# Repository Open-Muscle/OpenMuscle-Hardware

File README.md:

# 🛠️ OpenMuscle-Hardware (Deprecated)

> ⚠️ **This repository is no longer maintained.**  
> All hardware design files have been **moved to dedicated repositories** for each OpenMuscle device.  
> Please use the links below to access the latest versions, schematics, and BOMs.

---

## 📦 Where to Find Active Repositories

| Device | Description | New Repo |
|--------|-------------|----------|
| **FlexGrid** | 60-sensor modular wearable (successor to OM-12) | [OpenMuscle-FlexGrid](https://github.com/Open-Muscle/OpenMuscle-FlexGrid) |
| **LASK5** | Handheld labeler wand for gesture training | [OpenMuscle-LASK5](https://github.com/Open-Muscle/OpenMuscle-LASK5) |
| **OM-12** | Legacy 12-sensor forearm band | [OpenMuscle-Band](https://github.com/Open-Muscle/OpenMuscle-Band) |
| **Firmware & Scripts** | MicroPython code for all devices | [OpenMuscle-Software](https://github.com/Open-Muscle/OpenMuscle-Software) |
| **Documentation** | Central hub with build guides & tutorials | [OpenMuscle-Hub](https://github.com/Open-Muscle/OpenMuscle-Hub) |

---

## 🧬 About This Repo

This repository originally contained hardware design files for two experimental devices:

- **OpenMuscle Labeler** – A handheld interface for labeling finger positions in machine learning datasets.
- **OpenMuscle Sensor Bracelet (OM-12)** – A pressure-based forearm sensor for capturing muscle signals.

These designs are preserved in their new locations above for better modularity and long-term maintainability.

---

## 🧾 Historical Reference

This repo includes:
- `Labeler/`: KiCad files and documents for early LASK prototypes
- `SensorBracelet/`: KiCad files and mechanical designs for OM-12
- `docs/`: Revision notes and changelogs

---

## 📜 License

This repository is licensed under the **CERN-OHL-S v2** (Strongly Reciprocal).

"""markdown
🔗 Learn more at the [Open Source Hardware Association (OSHWA)](https://www.oshwa.org/definition/)
"""

OpenMuscle is an OSHWA-Certified open hardware project  
**Certification UID:** US002537

---

## 🙌 Thank You

Thank you to everyone who starred, forked, contributed to, or studied this repository during its development phase.  
Please visit the [OpenMuscle GitHub Organization](https://github.com/Open-Muscle) to explore the new, modular layout and latest devices.

🧠 Built by [@TURFPTAx](https://github.com/turfptax) • Project home: [openmuscle.org](https://openmuscle.org)

## 🎥 Video Overview

Curious about the assembly process? Watch our detailed video guide covering both the Sensor Bracelet (OM-12) and Labeler (LASK5) builds:  
📺 **[Watch on YouTube](https://www.youtube.com/watch?v=DQQq6cplsOw)**

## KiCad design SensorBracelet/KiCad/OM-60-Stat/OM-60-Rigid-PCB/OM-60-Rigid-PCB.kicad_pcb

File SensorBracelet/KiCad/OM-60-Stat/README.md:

# OpenMuscle FlexGrid (v2.0)

**OpenMuscle FlexGrid** is a modular wearable sensor grid with 60 analog pressure sensors arranged in a 15x4 matrix. It is the second-generation wearable in the OpenMuscle series and serves as the core interface for capturing muscle movement in prosthetic and robotics applications.

📍 Project Page: [openmuscle.org](https://openmuscle.org)

---

## 📐 System Overview

- **Sensor Grid**: 15 columns × 4 rows of Velostat pads
- **Flex PCB**: Thin and wearable with 21-pin output header
- **Rigid PCB**: ESP32-S3, haptic feedback, USB-C charging, multiplexer, OLED, IMU

---

## 🔧 Key Features

| Feature               | Description                                  |
|-----------------------|----------------------------------------------|
| MCU                   | ESP32-S3 (USB + BLE + ADC1)                  |
| Sensor Matrix         | 15×4 Velostat with voltage divider setup     |
| Multiplexer           | 74HC4067 (16-channel, 15 used)               |
| Row Reads             | 4x analog inputs on ADC1                     |
| OLED Display          | SSD1306 128x32 over I2C                      |
| IMU                   | ICM-42688-P 6-DOF sensor (optional)          |
| Haptic Feedback       | Motor driven by IRLML2060 MOSFET             |
| Power Management      | MAX16054 soft latch, TPS7A0333 LDO, LTC4054 LiPo charger |

---

## 🗂️ File Structure

```graphql
FlexGrid/
├── KiCad/ # Schematic and layout files
├── Images/ # Renders and photos
├── BOM.xlsx # Bill of materials (optional)
└── README.md # You're reading it!
```

# 📁 Repository Layout

```graphql
OpenMuscle-FlexGrid/
├── firmware/           # MicroPython or C code for scanning and I/O
├── hardware/
│   ├── KiCad/          # Schematics, PCB, BOMs
│   └── Images/         # Renders and assembly diagrams
├── docs/
│   └── Datasheets/     # ICs and reference materials
└── README.md
```
---

## 🛠️ How It Works

The 74HC4067 connects one column at a time to 3.3V. The Velostat pads act as pressure-sensitive resistors connected to row lines, which are pulled down with 10kΩ resistors and read via analog inputs.

A software loop cycles through all 15 columns, sampling all 4 rows each time for 60 total readings per frame.

---

## 🧪 Status

- ✅ Schematic Complete
- ✅ PCB Fabricated & Assembled
- 🛠️ Firmware In Progress
- 🧠 ML Integration Pipeline Active

---

## 🔗 Related Projects

- [SensorBracelet (OM-12)](../SensorBracelet/)
- [Labeler (LASK5)](../Labeler/)

---

## 📝 License

- **Hardware**: CERN-OHL-P v2
- **Software/Firmware**: MIT

---

## 🤝 Get Involved

We welcome contributions, feedback, and forks. This project is part of a broader mission to open-source biomechanical sensing tools for all.

Visit **[openmuscle.org](https://openmuscle.org)** or join our Discord (link coming soon).

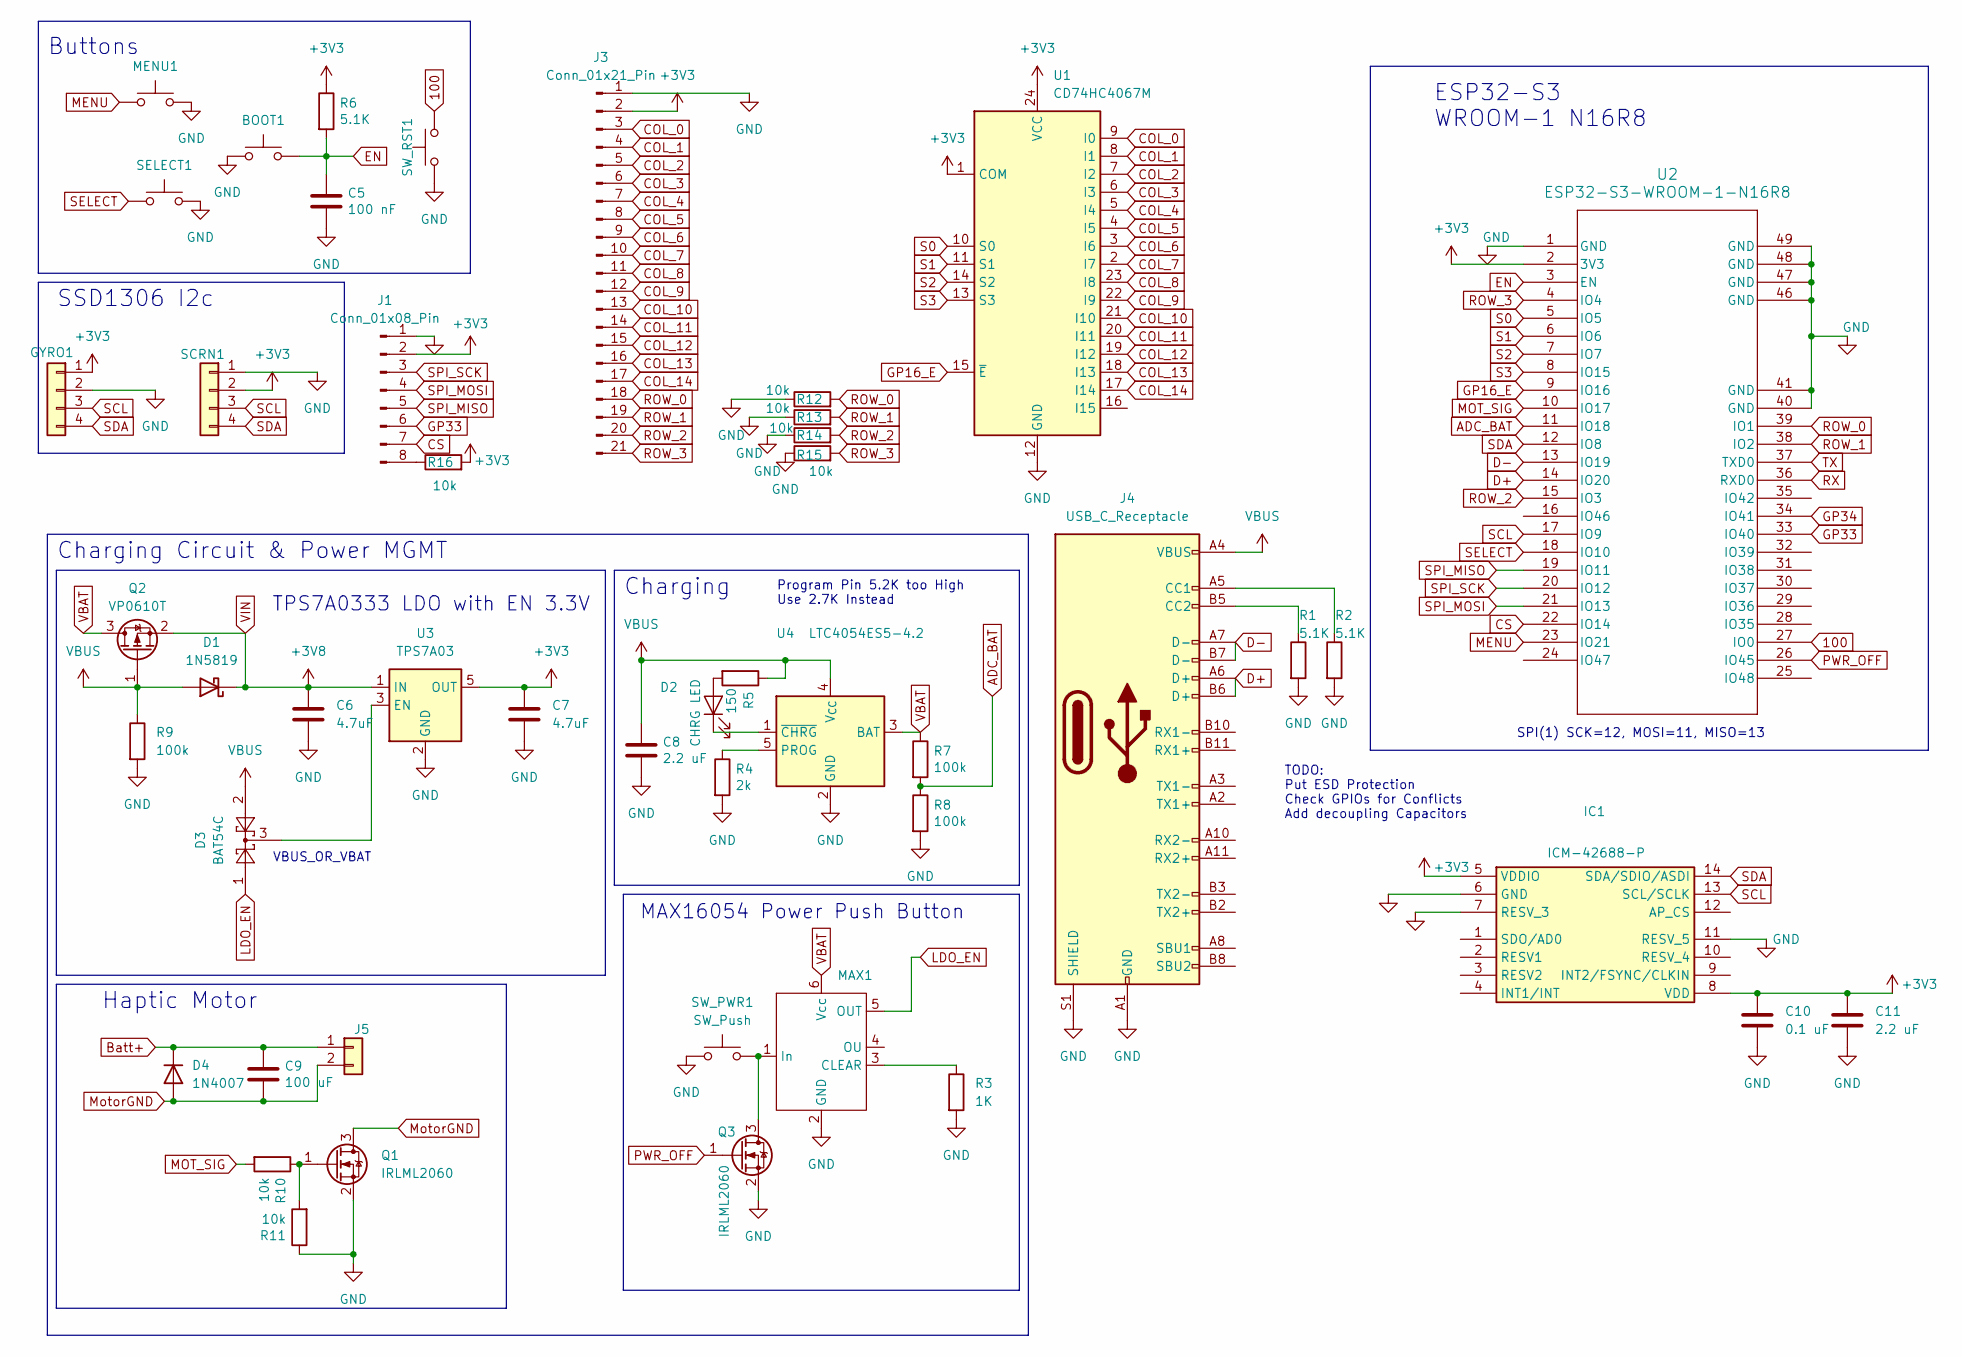
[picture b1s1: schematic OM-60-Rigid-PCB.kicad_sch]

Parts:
BOOT1: SW_Push; EVQP2P02M
C5: 100 nF; C_0402_1005Metric; JLCPN C1525
C6, C7: 4.7uF; C_0805_2012Metric
C8: 2.2 uF; C_0603_1608Metric; JLCPN C12530
C9: 100 uF; C_0603_1608Metric; JLCPN C12530
C10: 0.1 uF; C_0603_1608Metric
C11: 2.2 uF; C_0603_1608Metric
D1: 1N5819; D_SOD-123F
D2: CHRG LED; LED_0805_2012Metric; JLCPN C72043
D3: BAT54C; SOT-23
D4: 1N4007; D_SOD-123
GYRO1: Conn_01x04; PinHeader_1x04_P2.54mm_Vertical
IC1: ICM-42688-P; IIM42352; Mouser Part Number 410-ICM-42688-P
J1: Conn_01x08_Pin; PinHeader_1x08_P2.54mm_Vertical
J3: Conn_01x21_Pin; PinSocket_1x21_P2.54mm_Vertical
J4: USB_C_Receptacle; USB_C_Receptacle_HRO_TYPE-C-31-M-12
J5: Conn_01x02; PinHeader_1x02_P2.00mm_Vertical
MAX1: SOT-23-6
MENU1: SW_Push; EVQP2P02M
Q1, Q3: IRLML2060; SOT-23
Q2: VP0610T; SOT-23
R1, R2, R6: 5.1K; R_0603_1608Metric; JLCPN C25905
R3: 1K; R_0603_1608Metric
R4: 2k; R_0603_1608Metric; JLCPN C25905
R5: 150; R_0603_1608Metric; JLCPN C4109
R7, R8: 100k; R_0603_1608Metric; JLCPN C25905
R9: 100k; R_0603_1608Metric
R10, R11: 10k; R_0603_1608Metric; JLCPN C25744
R12, R13, R14, R15, R16: 10k; R_0603_1608Metric; JLCPN C25905
SCRN1: Conn_01x04; PinHeader_1x04_P2.54mm_Vertical
SELECT1: SW_Push; EVQP2P02M
SW_PWR1: SW_Push; EVQP2P02M
SW_RST1: SW_Push; EVQP2P02M
U1: CD74HC4067M; SOIC-24W_7.5x15.4mm_P1.27mm
U2: ESP32-S3-WROOM-1-N16R8
U3: TPS7A03; SOT-23-5
U4: LTC4054ES5-4.2; TSOT-23-5

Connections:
100: SW_RST1.2, U2.27 (IO0)
+3V3: C7.1, C10.1, C11.1, GYRO1.1, IC1.5 (VDDIO), IC1.8 (VDD), J1.2, J3.2, R6.1, R16.2, SCRN1.2, U1.1 (COM), U1.24 (VCC), U2.2 (3V3), U3.5 (OUT)
ADC_BAT: R7.2, R8.1, U2.11 (IO18)
Batt+: C9.2, D4.1 (K), J5.1
COL_0: J3.3, U1.9 (I0)
COL_1: J3.4, U1.8 (I1)
COL_2: J3.5, U1.7 (I2)
COL_3: J3.6, U1.6 (I3)
COL_4: J3.7, U1.5 (I4)
COL_5: J3.8, U1.4 (I5)
COL_6: J3.9, U1.3 (I6)
COL_7: J3.10, U1.2 (I7)
COL_8: J3.11, U1.23 (I8)
COL_9: J3.12, U1.22 (I9)
COL_10: J3.13, U1.21 (I10)
COL_11: J3.14, U1.20 (I11)
COL_12: J3.15, U1.19 (I12)
COL_13: J3.16, U1.18 (I13)
COL_14: J3.17, U1.17 (I14)
CS: J1.7, U2.22 (IO14)
D+: J4.A6 (D+), J4.B6 (D+), U2.14 (IO20)
D-: J4.A7 (D-), J4.B7 (D-), U2.13 (IO19)
EN: BOOT1.2, C5.2, R6.2, U2.3 (EN)
GND: BOOT1.1, C5.1, C6.2, C7.2, C8.1, C10.2, C11.2, GYRO1.2, IC1.6 (GND), IC1.7 (RESV_3), IC1.11 (RESV_5), J1.1, J3.1, J4.A1 (GND), J4.A12 (GND), J4.B1 (GND), J4.B12 (GND), J4.S1 (SHIELD), MAX1.2 (GND), MENU1.2, Q1.2 (S), Q3.2 (S), R1.2, R2.2, R3.2, R4.2, R8.2, R9.2, R11.1, R12.1, R13.1, R14.1, R15.1, SCRN1.1, SELECT1.2, SW_PWR1.1, SW_RST1.1, U1.12 (GND), U2.1 (GND), U2.40 (GND), U2.41 (GND), U2.46 (GND), U2.47 (GND), U2.48 (GND), U2.49 (GND), U3.2 (GND), U4.2 (GND)
GP16_E: U1.15 (~E), U2.9 (IO16)
GP33: J1.6, U2.33 (IO40)
GP34: U2.34 (IO41)
LDO_EN: D3.1, MAX1.5 (OUT)
MENU: MENU1.1, U2.23 (IO21)
MOT_SIG: R10.2, U2.10 (IO17)
MotorGND: C9.1, D4.2 (A), J5.2, Q1.3 (D)
unnamed: D2.2 (A), R5.2
unnamed: D2.1 (K), U4.1 (~CHRG)
unnamed: J1.8, R16.1
unnamed: J4.A5 (CC1), R2.1
unnamed: J4.B5 (CC2), R1.1
unnamed: MAX1.3 (CLEAR), R3.1
unnamed: MAX1.1 (In), Q3.3 (D), SW_PWR1.2
unnamed: Q1.1 (G), R10.1, R11.2
unnamed: D3.3, U3.3 (EN)
unnamed: R4.1, U4.5 (PROG)
PWR_OFF: Q3.1 (G), U2.26 (IO45)
ROW_0: J3.18, R12.2, U2.39 (IO1)
ROW_1: J3.19, R13.2, U2.38 (IO2)
ROW_2: J3.20, R14.2, U2.15 (IO3)
ROW_3: J3.21, R15.2, U2.4 (IO4)
RX: U2.36 (RXD0)
S0: U1.10 (S0), U2.5 (IO5)
S1: U1.11 (S1), U2.6 (IO6)
S2: U1.14 (S2), U2.7 (IO7)
S3: U1.13 (S3), U2.8 (IO15)
SCL: GYRO1.3, IC1.13 (SCL/SCLK), SCRN1.3, U2.17 (IO9)
SDA: GYRO1.4, IC1.14 (SDA/SDIO/ASDI), SCRN1.4, U2.12 (IO8)
SELECT: SELECT1.1, U2.18 (IO10)
SPI_MISO: J1.5, U2.19 (IO11)
SPI_MOSI: J1.4, U2.21 (IO13)
SPI_SCK: J1.3, U2.20 (IO12)
TX: U2.37 (TXD0)
VBAT: MAX1.6 (Vcc), Q2.3 (D), R7.1, U4.3 (BAT)
VBUS: C8.2, D1.2 (A), D3.2, J4.A4 (VBUS), J4.A9 (VBUS), J4.B4 (VBUS), J4.B9 (VBUS), Q2.1 (G), R5.1, R9.1, U4.4 (V_{CC})
VIN: C6.1, D1.1 (K), Q2.2 (S), U3.1 (IN)

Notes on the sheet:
Charging Circuit & Power MGMT
Haptic Motor
Buttons
ESP32-S3 WROOM-1 N16R8
TODO: Put ESD Protection Check GPIOs for Conflicts Add decoupling Capacitors
TPS7A0333 LDO with EN 3.3V
SPI(1) SCK=12, MOSI=11, MISO=13
SSD1306 I2c
Program Pin 5.2K too High Use 2.7K Instead
MAX16054 Power Push Button
VBUS_OR_VBAT
Charging

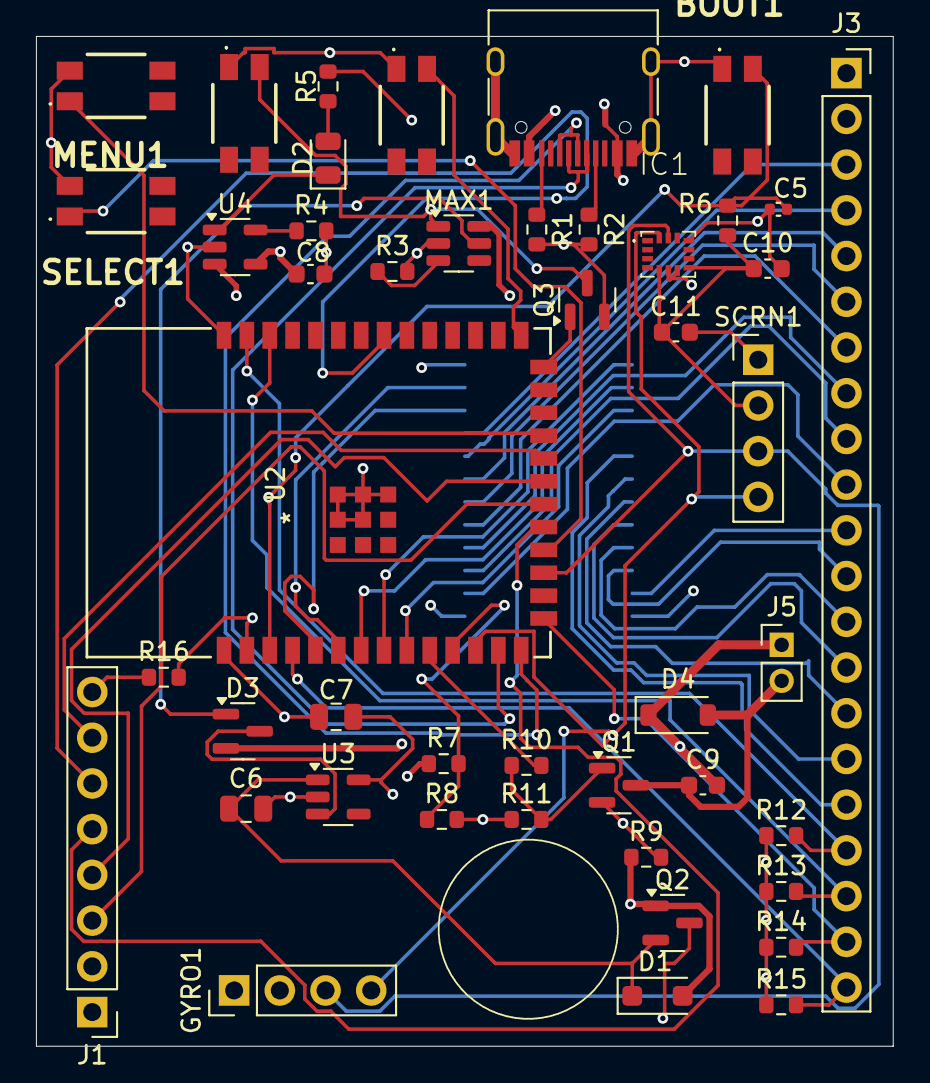
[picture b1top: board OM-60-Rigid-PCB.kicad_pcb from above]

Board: 4 copper layers, 47.6 x 56.1 mm, 47 parts (1 on the bottom side), 58 nets.

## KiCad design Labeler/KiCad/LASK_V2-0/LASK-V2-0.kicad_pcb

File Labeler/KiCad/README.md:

# LASK5 – OpenMuscle Sensor Device

**Version:** `V3 (Proposed)`  
**Target Microcontroller:** ESP32-S3-WROOM-1-N16R8  
**Project:** OpenMuscle – Biomechanical Sensing for Prosthetics & Robotics  
**Repository:** https://github.com/turfptax/OpenMuscle-Hardware

---

## 📐 Overview

The LASK5 board is a wearable sensor platform for real-time finger movement detection, developed as part of the OpenMuscle project. It integrates Hall effect sensors, a joystick, buttons, a low-power screen, and wireless communication via ESP32-S3.

Version 3 introduces multiple improvements in usability, sensing accuracy, and expandability.

---

## 🚀 New in V3 (Proposed)

| Feature | Description |
|--------|-------------|
| 🔌 USB Detection | VBUS now routed to a GPIO via voltage divider, allowing firmware to detect USB connection. |
| 🔋 USB Boot Without Battery | Modified power logic enables powering on via USB without a battery installed, using diode-based OR logic to control LDO enable line. |
| 📉 Improved ADC Accuracy | Voltage divider for battery monitoring updated to 10k/10k, reducing impedance for better ESP32-S3 ADC readings. |
| 🧭 6-Axis Gyroscope Support | IMU footprint and I²C headers added for optional motion sensing (MPU6050 or ICM-42688). |
| ⚙️ Charging Status Feedback | CHRG pin from LTC4054 connected to GPIO for in-software charge status indication. |

---
## 📦 Block Diagram
```
Battery ─────┐
├─> Charger (LTC4054) ──> Power Rail (+3.3V)
USB ───────┐ │
│ └─> VBUS GPIO (USB Detect)
└───> LDO EN Logic ──> TPS7A0333 LDO ──> ESP32-S3
```
---

## 📊 Hardware Specifications

- **MCU:** ESP32-S3-WROOM-1-N16R8 (dual-core, WiFi/BLE, 16MB flash, 8MB PSRAM)
- **Power:**
  - USB-C with VBUS detection
  - 1-cell LiPo battery
  - TPS7A0333 LDO (3.3V, low quiescent current)
  - MAX16054 latched soft-power button
- **Sensing:**
  - 4x Hall effect analog sensors
  - 1x Joystick (XY + button)
  - 0.96” SSD1306 OLED display (I²C)
  - Optional 6-axis gyro (MPU6050, ICM-42688, etc.)
- **Inputs:**
  - `menu` and `select` tactile buttons
  - Power button
- **Charging:**
  - LTC4054ES5-4.2 Li-Ion charger
  - CHRG status indicator routed to GPIO
- **Communication:**
  - ESP-NOW, WiFi, BLE
- **Headers:**
  - I²C breakout
  - SPI/debug/jumper expansion

---

## 🛠️ Setup & Firmware

- Flash via USB-C using esptool or Micropython.
- Default I²C pins: `SDA=GPIO15`, `SCL=GPIO16`
- ADC battery read: `GPIO4` (adjusted via voltage divider)
- USB detect pin: `GPIO10` *(example)*
- CHRG detect pin: `GPIO11` *(example)*

---

## 📚 Resources

- [OpenMuscle.org](https://openmuscle.org)
- [KiCad Schematic Viewer](https://kicad.org)
- [ESP32-S3 Datasheet](https://www.espressif.com/sites/default/files/documentation/esp32-s3_datashee---

## 🙌 Contributing

Interested in testing or improving the hardware? Submit a pull request or open an issue with your suggestions.

---

## 🧪 Version History

| Version | Date | Notes |
|---------|------|-------|
| V1 | 2024-02 | Initial prototype, using ESP32-S3 Dev-Kit |
| V2 | 2024-05 | 4-Layer PCB with 4x1 Hall sensors & Joystick |
| V3 | 25-XX | USB logic, gyro, and ADC improvements |

---

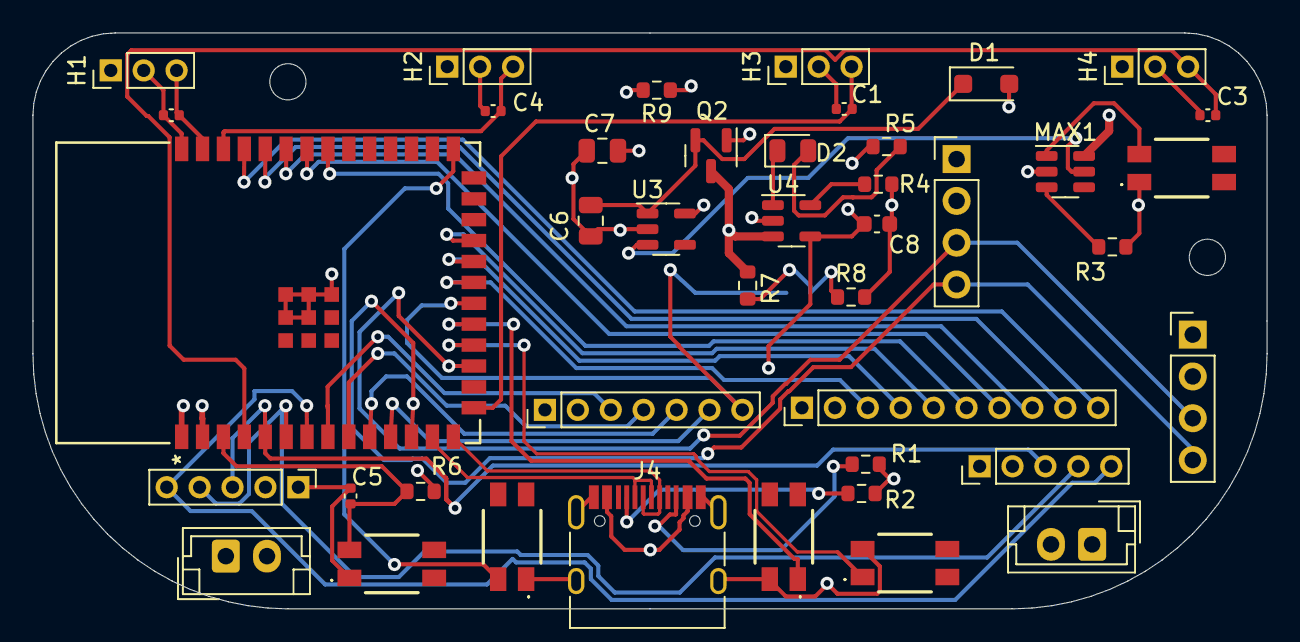
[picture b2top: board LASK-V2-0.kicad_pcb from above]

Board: 4 copper layers, 75.0 x 35.0 mm, 45 parts (1 on the bottom side), 42 nets.

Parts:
BattExtLTC4054: JST_02; JST_EH_B2B-EH-A_1x02_P2.50mm_Vertical
C1, C2, C3, C4, C5: 100 nF; C_0402_1005Metric
C6, C7: 4.7uF; C_0805_2012Metric
C8: 2.2 uF; C_0603_1608Metric
D1: 1N5819; D_SOD-123F
D2: LED GREEN; LED_0805_2012Metric
H1, H2, H3, H4: A1369xUA-10; PinHeader_1x03_P2.00mm_Vertical
H7, H8: MountingHole; MountingHole_2.2mm_M2
J1, J9: Conn_01x04; PinHeader_1x04_P2.54mm_Vertical
J2: JST_02; JST_EH_B2B-EH-A_1x02_P2.50mm_Vertical
J3: Conn_01x10_Pin; PinHeader_1x10_P2.00mm_Vertical
J4: USB_C_Receptacle; USB_C_Receptacle_HRO_TYPE-C-31-M-12
J6: Conn_01x07_Pin; PinHeader_1x07_P2.00mm_Vertical
JP1: Jumper_2_Open; SolderJumper-2_P1.3mm_Open_TrianglePad1.0x1.5mm
Joystick1, Joystick2: Conn_01x05_Pin; PinHeader_1x05_P2.00mm_Vertical
MAX1: SOT-23-6
Q2: VP0610T; SOT-23
R1, R2, R6: 5.1K; R_0603_1608Metric
R3: 1K; R_0603_1608Metric
R4: 2k; R_0603_1608Metric
R5: 150; R_0603_1608Metric
R7, R8, R9: 100k; R_0603_1608Metric
SW_BOOT1: SW_Push; EVQP2P02M
SW_M1: SW_Push; EVQP2P02M
SW_PWR1: SW_Push; EVQP2P02M
SW_RST1: SW_Push; EVQP2P02M
SW_SEL1: SW_Push; EVQP2P02M
U2: ESP32-S3-WROOM-1-N16R8; ESP32-S3-WROOM-1_EXP
U3: TPS7A03; SOT-23-5
U4: LTC4054ES5-4.2; TSOT-23-5

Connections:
100: SW_RST1.2, U2.27 (IO0)
+3V3: C7.1, H1.1 (VCC), H2.1 (VCC), H3.1 (VCC), H4.1 (VCC), J1.2, J3.2, J6.2, J9.2, Joystick1.2, Joystick2.2, R6.1, U2.2 (3V3), U3.5 (OUT)
ADC_BAT: J6.7, JP1.2 (B), U2.20 (IO12)
D+: J4.A6 (D+), J4.B6 (D+), U2.14 (IO20)
D-: J4.A7 (D-), J4.B7 (D-), U2.13 (IO19)
EN: C5.2, R6.2, SW_BOOT1.2, U2.3 (EN)
GND: BattExtLTC4054.2, C1.1, C2.1, C3.1, C4.1, C5.1, C6.2, C7.2, C8.1, H1.2 (GND), H2.2 (GND), H3.2 (GND), H4.2 (GND), J1.1, J2.2, J3.1, J4.A1 (GND), J4.A12 (GND), J4.B1 (GND), J4.B12 (GND), J4.S1 (SHIELD), J6.1, J9.1, Joystick1.1, Joystick2.1, MAX1.2 (GND), R1.2, R2.2, R3.2, R4.2, R8.2, R9.2, SW_BOOT1.1, SW_M1.2, SW_PWR1.1, SW_RST1.1, SW_SEL1.2, U2.1 (GND), U2.40 (GND), U2.41 (GND), U2.46 (GND), U2.47 (GND), U2.48 (GND), U2.49 (GND), U3.2 (GND), U4.2 (GND)
GP13: J3.3, U2.21 (IO13)
GP14: J3.4, U2.22 (IO14)
GP15: J6.3, U2.8 (IO15)
GP16: J6.4, U2.9 (IO16)
GP17: J6.5, U2.10 (IO17)
GP18: J6.6, U2.11 (IO18)
GP21: J3.5, U2.23 (IO21)
GP33: J3.6, U2.33 (IO40)
GP34: J3.7, U2.34 (IO41)
GP42: J3.8, U2.35 (IO42)
JSW: Joystick1.5, Joystick2.5, U2.7 (IO7)
JX: Joystick1.3, Joystick2.3, U2.5 (IO5)
JY: Joystick1.4, Joystick2.4, U2.6 (IO6)
LDO_EN: MAX1.5 (OUT), U3.3 (EN)
unnamed: D2.2 (A), R5.2
unnamed: D2.1 (K), U4.1 (~CHRG)
unnamed: J4.A5 (CC1), R2.1
unnamed: J4.B5 (CC2), R1.1
unnamed: JP1.1 (A), R7.2, R8.1
unnamed: MAX1.3 (CLEAR), R3.1
unnamed: MAX1.1 (In), SW_PWR1.2
unnamed: R4.1, U4.5 (PROG)
RX: J3.9, U2.36 (RXD0)
SCL: J1.3, J9.3, U2.17 (IO9)
SDA: J1.4, J9.4, U2.12 (IO8)
TX: J3.10, U2.37 (TXD0)
VBAT: BattExtLTC4054.1, J2.1, MAX1.6 (Vcc), Q2.3 (D), R7.1, U4.3 (BAT)
VBUS: C8.2, D1.2 (A), J4.A4 (VBUS), J4.A9 (VBUS), J4.B4 (VBUS), J4.B9 (VBUS), Q2.1 (G), R5.1, R9.1, U4.4 (V_{CC})
VIN: C6.1, D1.1 (K), Q2.2 (S), U3.1 (IN)
b_select: SW_SEL1.1, U2.18 (IO10)
b_start: SW_M1.1, U2.19 (IO11)
hall_0: C2.2, H1.3 (VOUT), U2.39 (IO1)
hall_1: C4.2, H2.3 (VOUT), U2.38 (IO2)
hall_2: C1.2, H3.3 (VOUT), U2.15 (IO3)
hall_3: C3.2, H4.3 (VOUT), U2.4 (IO4)

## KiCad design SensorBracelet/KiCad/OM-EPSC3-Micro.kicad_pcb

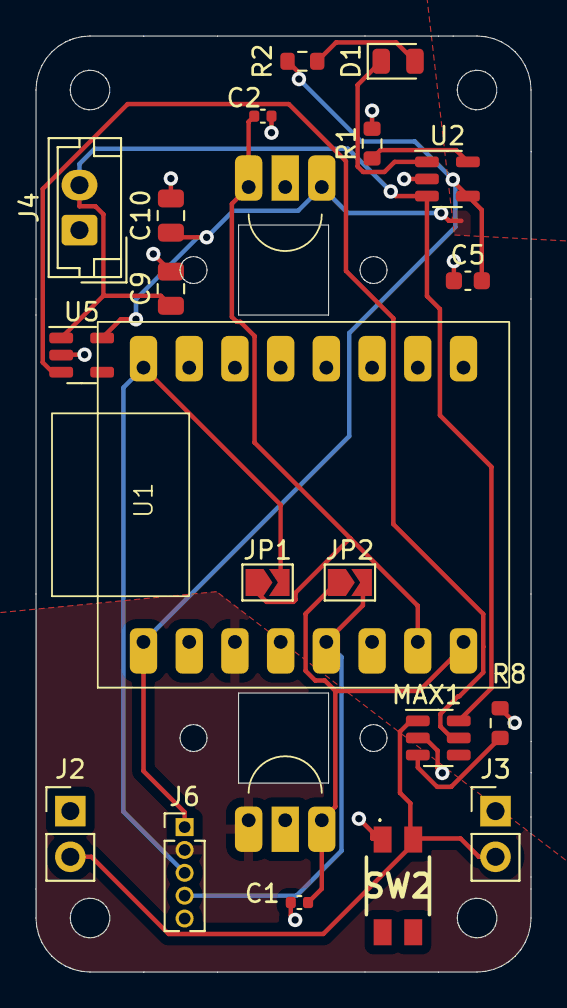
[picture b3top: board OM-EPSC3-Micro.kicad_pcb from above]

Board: 2 copper layers, 27.5 x 52.0 mm, 22 parts (0 on the bottom side), 14 nets.

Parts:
C1, C2: 100 nF; C_0402_1005Metric
C5: 2.2 uF; C_0603_1608Metric
C9, C10: 4.7uF; C_0805_2012Metric
D1: LED GREEN; LED_0805_2012Metric
H0, H1: A1369xUA-10; Hall49E
J2, J3: Conn_01x02_Pin; PinHeader_1x02_P2.54mm_Vertical
J4: JST_02; JST_EH_B2B-EH-A_1x02_P2.50mm_Vertical
J6: Conn_01x05_Pin; PinHeader_1x05_P1.27mm_Vertical
JP1, JP2: SolderJumper_2_Open; SolderJumper-2_P1.3mm_Open_TrianglePad1.0x1.5mm
MAX1: SOT-23-6
R1: 2.7k; R_0603_1608Metric
R2: 150; R_0603_1608Metric
R8: 1K; R_0603_1608Metric
SW2: SW_Push; EVQP2P02M
U1: ESP32-C3-Super Mini
U2: LTC4054ES5-4.2; TSOT-23-5
U5: TPS7A03; SOT-23-5

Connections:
+3V3: C10.1, H0.1 (VCC), H1.1 (VCC), J6.2, U1.102 (3V3), U5.5 (OUT)
+3V8: C9.1, J4.1, MAX1.6 (Vcc), U2.3 (BAT), U5.1 (IN)
+5V: C5.2, J6.1, R2.1, U1.100 (5V), U2.4 (V_{CC})
ADC2: J6.4, JP2.2 (B), U1.3 (GPIO3)
ADC3: J6.3, JP1.2 (B), U1.5 (GPIO5)
GND: C1.1, C2.1, C5.1, C9.2, C10.2, H0.2 (GND), H1.2 (GND), J2.1, J3.1, J4.2, J6.5, MAX1.2 (GND), R1.2, R8.2, SW2.1, U1.101 (GND), U2.2 (GND), U5.2 (GND)
LDO_EN: MAX1.5 (OUT), U5.3 (EN)
unnamed: D1.2 (A), R2.2
unnamed: D1.1 (K), U2.1 (~CHRG)
unnamed: MAX1.3 (CLEAR), R8.1
unnamed: R1.1, U2.5 (PROG)
RMT-BTN: J2.2, J3.2, MAX1.1 (In), SW2.2
hall_0: C1.2, H0.3 (VOUT), JP2.1 (A), U1.0 (GPIO0)
hall_1: C2.2, H1.3 (VOUT), JP1.1 (A), U1.1 (GPIO1)

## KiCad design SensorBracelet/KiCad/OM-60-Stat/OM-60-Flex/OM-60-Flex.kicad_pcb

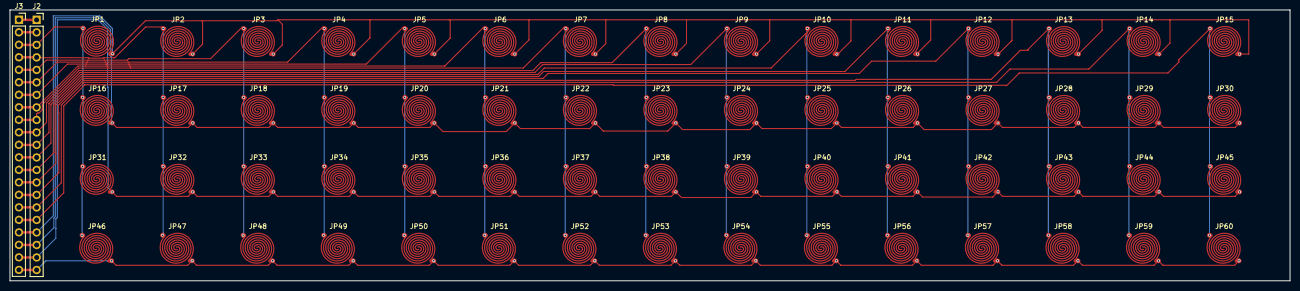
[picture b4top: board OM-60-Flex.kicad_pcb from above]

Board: 2 copper layers, 260.0 x 55.0 mm, 62 parts (0 on the bottom side), 21 nets.

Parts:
J2, J3: Conn_01x21_Pin; PinSocket_1x21_P2.54mm_Vertical
JP1, JP2, JP3, JP4, JP5, JP6, JP7, JP8, JP9, JP10, JP11, JP12, JP13, JP14, JP15, JP16, JP17, JP18, JP19, JP20, JP21, JP22, JP23, JP24, JP25, JP26, JP27, JP28, JP29, JP30, JP31, JP32, JP33, JP34, JP35, JP36, JP37, JP38, JP39, JP40, JP41, JP42, JP43, JP44, JP45, JP46, JP47, JP48, JP49, JP50, JP51, JP52, JP53, JP54, JP55, JP56, JP57, JP58, JP59, JP60: Jumper_2_Open; 10mmPad

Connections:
+3.3V: J2.2, J3.2
COL_0: J2.3, J3.3, JP1.1 (A), JP16.1 (A), JP31.1 (A), JP46.1 (A)
COL_1: J2.4, J3.4, JP2.1 (A), JP17.1 (A), JP32.1 (A), JP47.1 (A)
COL_2: J2.5, J3.5, JP3.1 (A), JP18.1 (A), JP33.1 (A), JP48.1 (A)
COL_3: J2.6, J3.6, JP4.1 (A), JP19.1 (A), JP34.1 (A), JP49.1 (A)
COL_4: J2.7, J3.7, JP5.1 (A), JP20.1 (A), JP35.1 (A), JP50.1 (A)
COL_5: J2.8, J3.8, JP6.1 (A), JP21.1 (A), JP36.1 (A), JP51.1 (A)
COL_6: J2.9, J3.9, JP7.1 (A), JP22.1 (A), JP37.1 (A), JP52.1 (A)
COL_7: J2.10, J3.10, JP8.1 (A), JP23.1 (A), JP38.1 (A), JP53.1 (A)
COL_8: J2.11, J3.11, JP9.1 (A), JP24.1 (A), JP39.1 (A), JP54.1 (A)
COL_9: J2.12, J3.12, JP10.1 (A), JP25.1 (A), JP40.1 (A), JP55.1 (A)
COL_10: J2.13, J3.13, JP11.1 (A), JP26.1 (A), JP41.1 (A), JP56.1 (A)
COL_11: J2.14, J3.14, JP12.1 (A), JP27.1 (A), JP42.1 (A), JP57.1 (A)
COL_12: J2.15, J3.15, JP13.1 (A), JP28.1 (A), JP43.1 (A), JP58.1 (A)
COL_13: J2.16, J3.16, JP14.1 (A), JP29.1 (A), JP44.1 (A), JP59.1 (A)
COL_14: J2.17, J3.17, JP15.1 (A), JP30.1 (A), JP45.1 (A), JP60.1 (A)
GND: J2.1, J3.1
ROW_0: J2.18, J3.18, JP1.2 (B), JP2.2 (B), JP3.2 (B), JP4.2 (B), JP5.2 (B), JP6.2 (B), JP7.2 (B), JP8.2 (B), JP9.2 (B), JP10.2 (B), JP11.2 (B), JP12.2 (B), JP13.2 (B), JP14.2 (B), JP15.2 (B)
ROW_1: J2.19, J3.19, JP16.2 (B), JP17.2 (B), JP18.2 (B), JP19.2 (B), JP20.2 (B), JP21.2 (B), JP22.2 (B), JP23.2 (B), JP24.2 (B), JP25.2 (B), JP26.2 (B), JP27.2 (B), JP28.2 (B), JP29.2 (B), JP30.2 (B)
ROW_2: J2.20, J3.20, JP31.2 (B), JP32.2 (B), JP33.2 (B), JP34.2 (B), JP35.2 (B), JP36.2 (B), JP37.2 (B), JP38.2 (B), JP39.2 (B), JP40.2 (B), JP41.2 (B), JP42.2 (B), JP43.2 (B), JP44.2 (B), JP45.2 (B)
ROW_3: J2.21, J3.21, JP46.2 (B), JP47.2 (B), JP48.2 (B), JP49.2 (B), JP50.2 (B), JP51.2 (B), JP52.2 (B), JP53.2 (B), JP54.2 (B), JP55.2 (B), JP56.2 (B), JP57.2 (B), JP58.2 (B), JP59.2 (B), JP60.2 (B)

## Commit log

2024-10-26 Open Muscle Dev Kit Files V0 and V1
    Main files for the Open Muscle Dev Kit which consists of a Labeler and a Sensor Band.
2024-10-27 Schematics and BOM
2025-04-12 Lask V2
2025-04-12 LASK5-V2 PCB
2025-04-13 LASK5-V2.1
2025-04-13 LASK5-V2.1 Updates
2025-04-13 V2 Artwork
2025-05-07 LASK5 V2 Hardware Update
    Working PCB for LASK5 V2
2025-05-07 LASK5 V2 Update
2025-05-07 LASK5 Hardware Revision V3 Proposal
    Hardware Revision: LASK5 V3 – USB Detection, Power-on Logic, Gyro Support, and ADC Accuracy Improvements
    Pull Request Summary:
    This proposed hardware update addresses limitations in the current LASK5 V2 schematic. The changes aim to improve usability, allow USB-powered operation without a battery, enhance ADC voltage reading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
2025-05-07 Create LICENSE.txt
    CERN Open Hardware License
2025-05-11 Or Power Switch Update
2025-05-19 LASK5 V3 and OM-FlexGrid

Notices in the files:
parts and their libraries:
Copyright 2016 Accelerated Designs. All rights reserved.
